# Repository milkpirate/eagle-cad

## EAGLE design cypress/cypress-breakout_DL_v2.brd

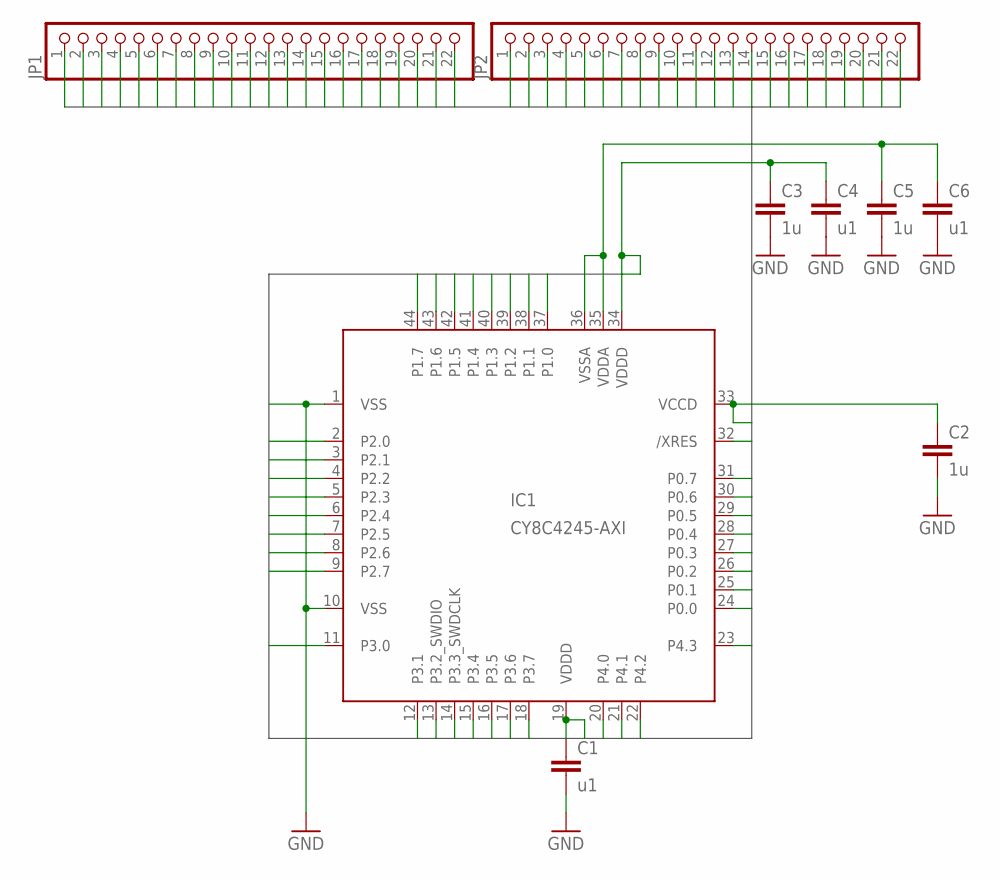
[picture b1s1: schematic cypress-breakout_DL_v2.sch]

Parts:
C1, C4, C6: u1; C0805K
C2, C3, C5: 1u; C0805K
IC1: CY8C4245-AXI; 44-TQFP-0.8
JP1, JP2: PINHD-1X22; 1X22

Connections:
#XRES: IC1.32 (/XRES), JP2.10
GND: C1.2, C2.2, C3.2, C4.2, C5.2, C6.2
P0.0: IC1.24 (P0.0), JP2.2
P0.1: IC1.25 (P0.1), JP2.3
P0.2: IC1.26 (P0.2), JP2.4
P0.3: IC1.27 (P0.3), JP2.5
P0.4: IC1.28 (P0.4), JP2.6
P0.5: IC1.29 (P0.5), JP2.7
P0.6: IC1.30 (P0.6), JP2.8
P0.7: IC1.31 (P0.7), JP2.9
P1.0: IC1.37 (P1.0), JP2.15
P1.1: IC1.38 (P1.1), JP2.16
P1.2: IC1.39 (P1.2), JP2.17
P1.3: IC1.40 (P1.3), JP2.18
P1.4: IC1.41 (P1.4), JP2.19
P1.5: IC1.42 (P1.5), JP2.20
P1.6: IC1.43 (P1.6), JP2.21
P1.7: IC1.44 (P1.7), JP2.22
P2.0: IC1.2 (P2.0), JP1.2
P2.1: IC1.3 (P2.1), JP1.3
P2.2: IC1.4 (P2.2), JP1.4
P2.3: IC1.5 (P2.3), JP1.5
P2.4: IC1.6 (P2.4), JP1.6
P2.5: IC1.7 (P2.5), JP1.7
P2.6: IC1.8 (P2.6), JP1.8
P2.7: IC1.9 (P2.7), JP1.9
P3.0: IC1.11 (P3.0), JP1.11
P3.1: IC1.12 (P3.1), JP1.12
P3.2: IC1.13 (P3.2_SWDIO), JP1.13
P3.3: IC1.14 (P3.3_SWDCLK), JP1.14
P3.4: IC1.15 (P3.4), JP1.15
P3.5: IC1.16 (P3.5), JP1.16
P3.6: IC1.17 (P3.6), JP1.17
P3.7: IC1.18 (P3.7), JP1.18
P4.0: IC1.20 (P4.0), JP1.20
P4.1: IC1.21 (P4.1), JP1.21
P4.2: IC1.22 (P4.2), JP1.22
P4.3: IC1.23 (P4.3), JP2.1
VCCD: C2.1, IC1.33 (VCCD), JP2.11
VDDA: C5.1, C6.1, IC1.35 (VDDA), JP2.13
VDDD: C1.1, C3.1, C4.1, IC1.19 (VDDD), IC1.34 (VDDD), JP1.19, JP2.12
VSS: IC1.1 (VSS), IC1.10 (VSS), JP1.1, JP1.10
VSSA: IC1.36 (VSSA), JP2.14

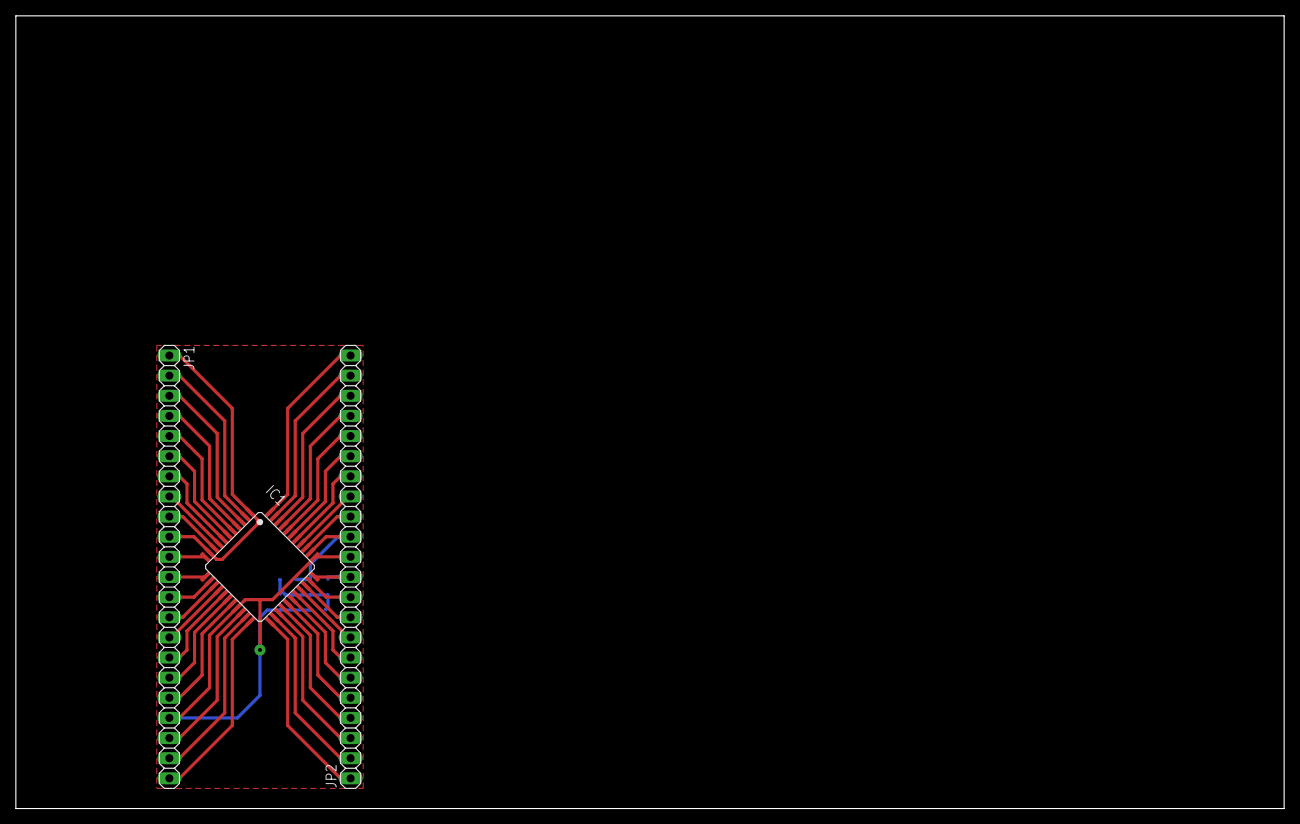
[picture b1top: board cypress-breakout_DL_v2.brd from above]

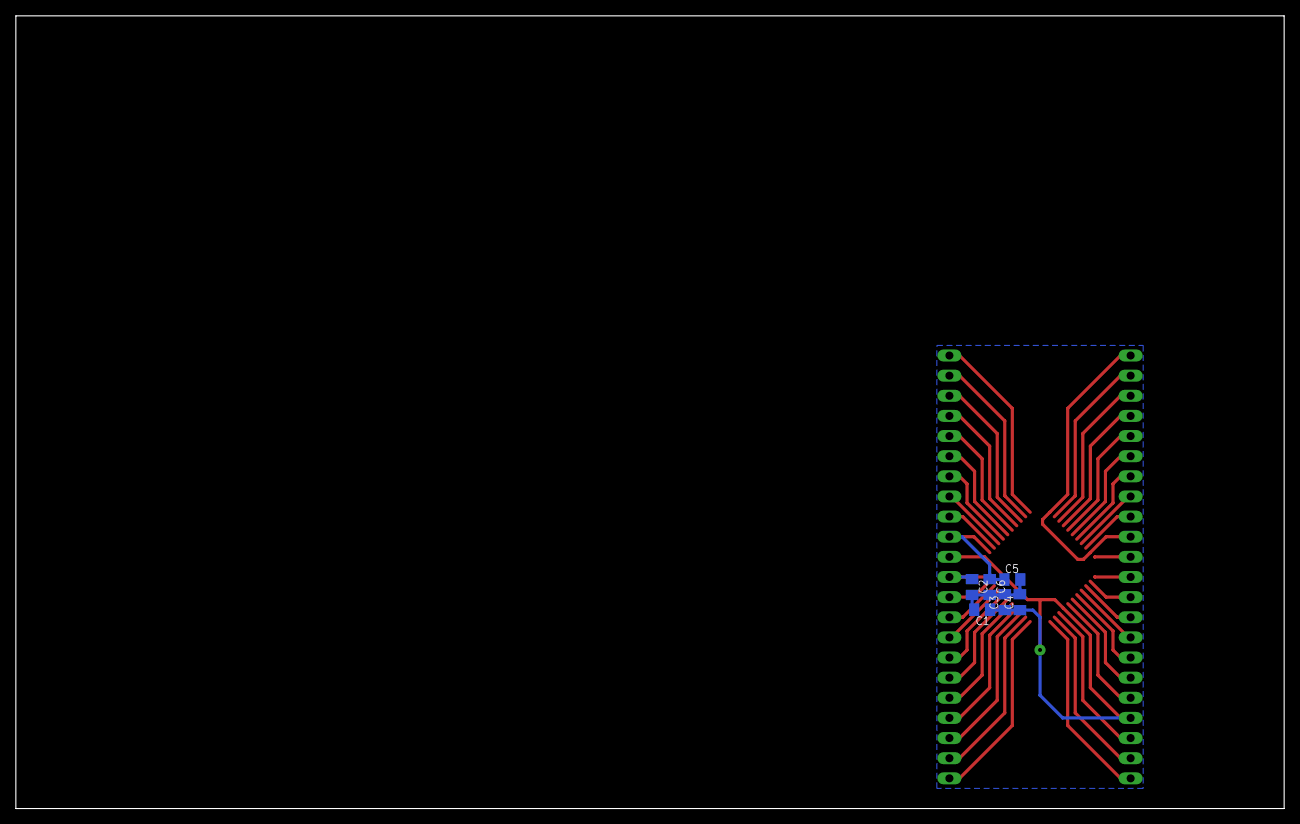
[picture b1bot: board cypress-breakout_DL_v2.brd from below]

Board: 2 copper layers, 160.0 x 100.0 mm, 9 parts (6 on the bottom side), 43 nets.

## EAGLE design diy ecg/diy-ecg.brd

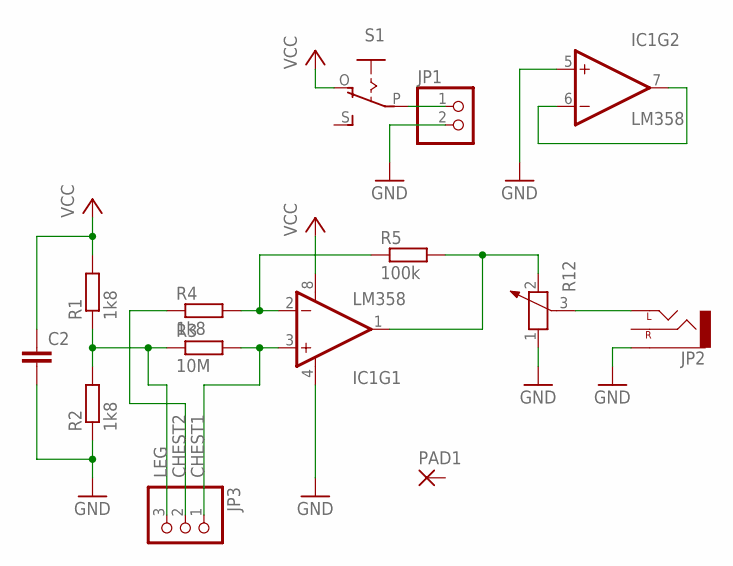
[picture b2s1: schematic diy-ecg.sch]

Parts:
C2: C-EU025-025X050; C025-025X050
IC1: LM358; DIP08
JP1: PINHD-1X2; 1X02
JP2: AUDIO-JACKPIN-HOLES; AUDIO-JACK-HOLES
JP3: PINHD-1X3; 1X03
PAD1: 3,81/1,4
R1, R2, R4: 1k8; 0204/7
R3: 10M; 0204/7
R5: 100k; 0204/7
R12: POTENTIOMETER_PT-10; PT-10
S1: EG1218S; EG1218

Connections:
CHEST1: IC1.3 (+IN), JP3.1, R3.2
CHEST2: JP3.2, R4.1
GND: C2.2, IC1.4 (V-), IC1.5 (+IN), JP1.2, JP2.GND (SLEEVE), R2.1, R12.1
LEG: JP3.3, R1.1, R2.2, R3.1
unnamed: JP1.1, S1.P
unnamed: IC1.1 (OUT), R5.2, R12.2
unnamed: IC1.2 (-IN), R4.2, R5.1
unnamed: IC1.6 (-IN), IC1.7 (OUT)
unnamed: JP2.L1- (LEFT), JP2.L2- (LEFT), R12.3
VCC: C2.1, IC1.8 (V+), R1.2, S1.O

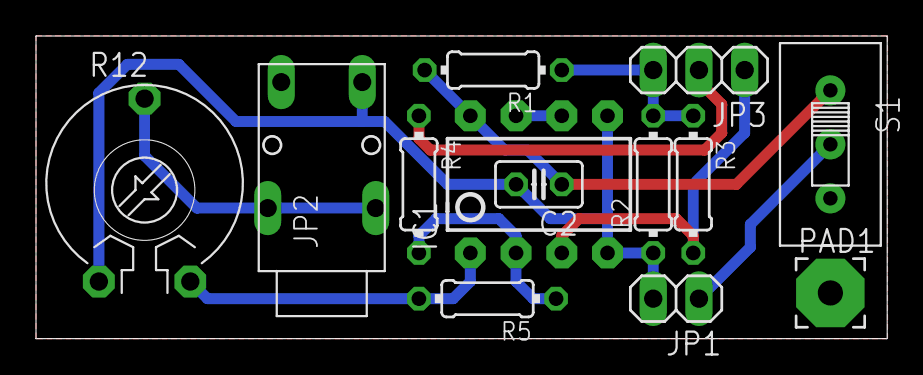
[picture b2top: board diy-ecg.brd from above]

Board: 2 copper layers, 47.3 x 16.8 mm, 13 parts (0 on the bottom side), 10 nets.

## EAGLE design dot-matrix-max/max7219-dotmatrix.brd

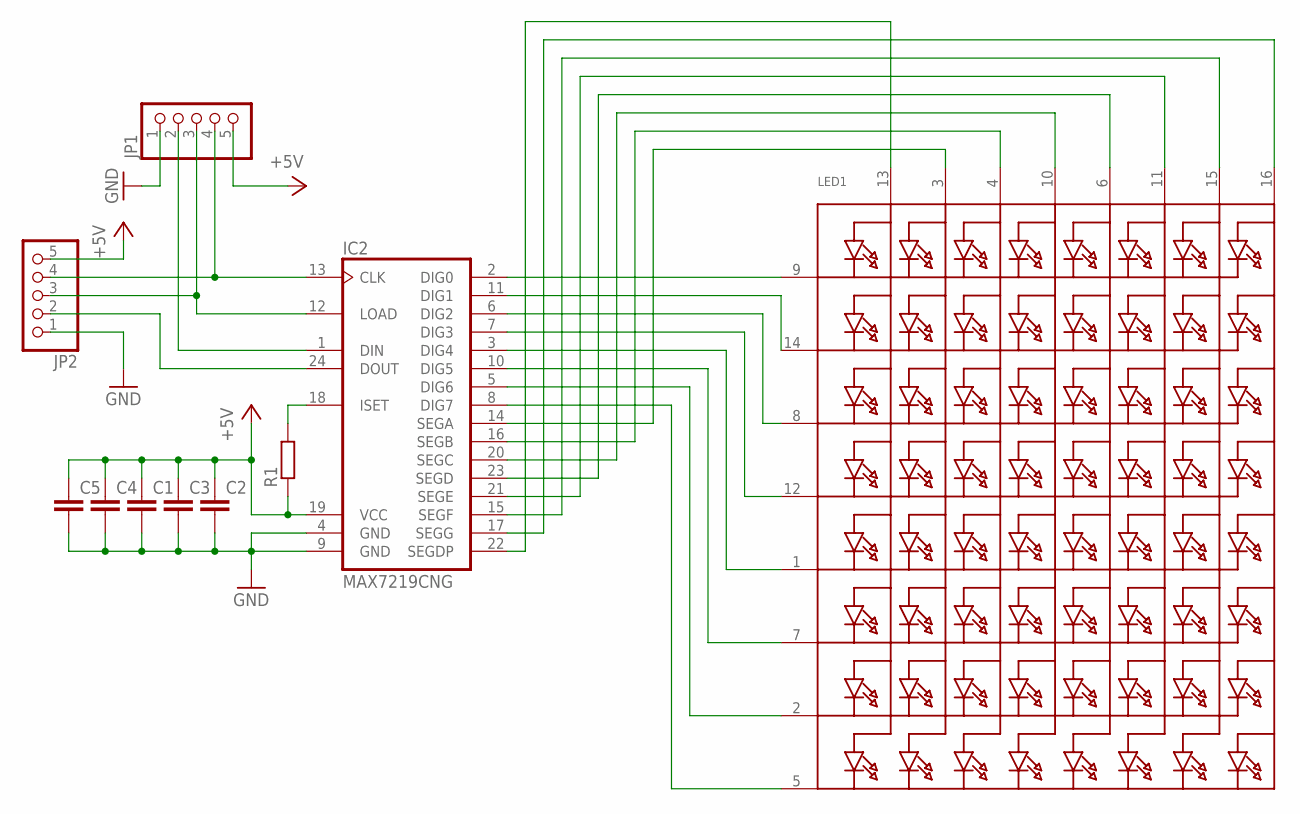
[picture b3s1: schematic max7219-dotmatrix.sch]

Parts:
C1, C2, C3, C4, C5: C-EUC0805K; C0805K
IC2: MAX7219CNG; DIL24-3
JP1, JP2: PINHD-1X5/90; 1X05/90
LED1: SEGMENT_8X8_ROWCATHODEM12A881UR; SEGMENT_BL-M12A881UR
R1: R-EU_M0805; M0805

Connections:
+5V: C1.1, C2.1, C3.1, C4.1, C5.1, IC2.19 (VCC), JP1.5, JP2.5, R1.1
GND: C1.2, C2.2, C3.2, C4.2, C5.2, IC2.4 (GND), IC2.9 (GND), JP1.1, JP2.1
unnamed: IC2.2 (DIG0), LED1.9 (K1)
unnamed: IC2.11 (DIG1), LED1.14 (K2)
unnamed: IC2.6 (DIG2), LED1.8 (K3)
unnamed: IC2.7 (DIG3), LED1.12 (K4)
unnamed: IC2.3 (DIG4), LED1.1 (K5)
unnamed: IC2.10 (DIG5), LED1.7 (K6)
unnamed: IC2.5 (DIG6), LED1.2 (K7)
unnamed: IC2.8 (DIG7), LED1.5 (K8)
unnamed: IC2.14 (SEGA), LED1.3 (A2)
unnamed: IC2.16 (SEGB), LED1.4 (A3)
unnamed: IC2.20 (SEGC), LED1.10 (A4)
unnamed: IC2.23 (SEGD), LED1.6 (A5)
unnamed: IC2.21 (SEGE), LED1.11 (A6)
unnamed: IC2.15 (SEGF), LED1.15 (A7)
unnamed: IC2.17 (SEGG), LED1.16 (A8)
unnamed: IC2.22 (SEGDP), LED1.13 (A1)
unnamed: IC2.24 (DOUT), JP2.2
unnamed: IC2.13 (CLK), JP1.4, JP2.4
unnamed: IC2.12 (LOAD), JP1.3, JP2.3
unnamed: IC2.18 (ISET), R1.2
unnamed: IC2.1 (DIN), JP1.2

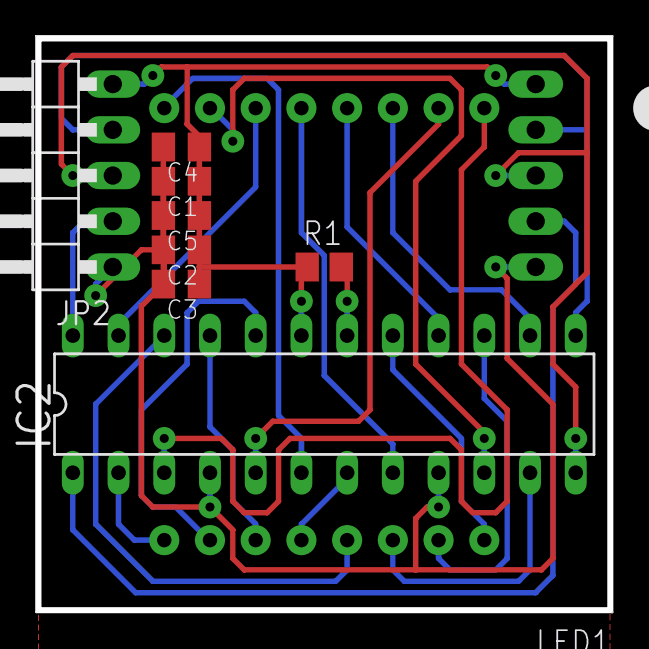
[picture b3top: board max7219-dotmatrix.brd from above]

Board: 2 copper layers, 31.7 x 31.7 mm, 10 parts (1 on the bottom side), 23 nets.

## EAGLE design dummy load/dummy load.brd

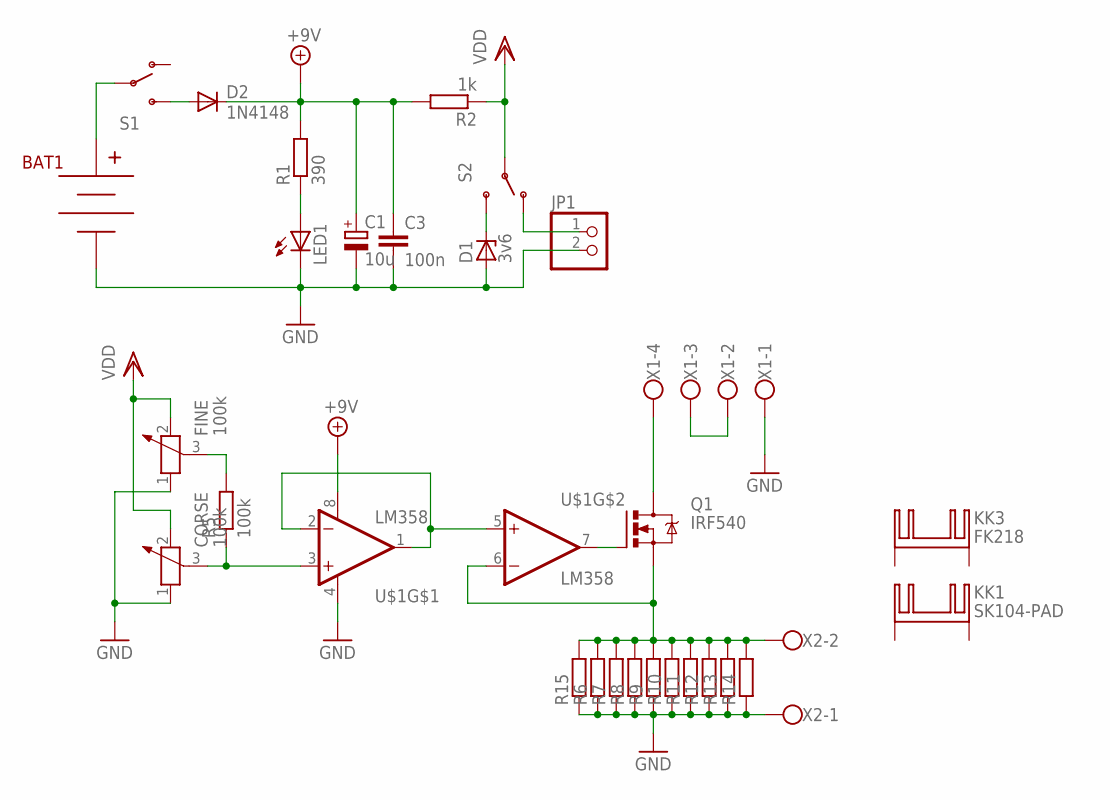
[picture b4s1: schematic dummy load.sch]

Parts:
BAT1: BC9VPC
C1: 10u; TT2D5L
C3: 100n; C025-025X050
CORSE: 100k; PT-10
D1: 3v6; ZDIO-5
D2: 1N4148; D-2.5
FINE: 100k; PT-10
JP1: PINHD-1X2; 1X02
KK1: SK104-PAD
KK3: FK218
LED1: LED5MM
Q1: IRF540; TO220BV
R1: 390; 0207/2V
R2: 1k; 0204/7
R5: 100k; 0204/7
R6, R7, R8, R9, R10, R11, R12, R13, R14, R15: R-EU_0207/7; 0207/7
S1, S2: SWITCH-SPSTPTH; SWITCH-SPDT
U$1: LM358; DIP08
X1: W237-4
X2: W237-102

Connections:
+9V: C1.+, C3.1, D2.C, R1.2, R2.2, U$1.8 (V+)
GND: BAT1.V-, C1.-, C3.2, CORSE.1, D1.A, FINE.1, JP1.2, LED1.K (C), R6.1, R7.1, R8.1, R9.1, R10.1, R11.1, R12.1, R13.1, R14.1, R15.1, U$1.4 (V-), X1.1, X2.1
unnamed: U$1.1 (OUT), U$1.2 (-IN), U$1.5 (+IN)
unnamed: CORSE.3, R5.1, U$1.3 (+IN)
unnamed: LED1.A, R1.1
unnamed: FINE.3, R5.2
unnamed: BAT1.V+, S1.2
unnamed: Q1.D, X1.4
unnamed: X1.2, X1.3
unnamed: D2.A, S1.3 (S)
unnamed: Q1.G, U$1.7 (OUT)
unnamed: D1.C, S2.3 (S)
unnamed: JP1.1, S2.1 (O)
unnamed: Q1.S, R6.2, R7.2, R8.2, R9.2, R10.2, R11.2, R12.2, R13.2, R14.2, R15.2, U$1.6 (-IN), X2.2
VDD: CORSE.2, FINE.2, R2.1, S2.2

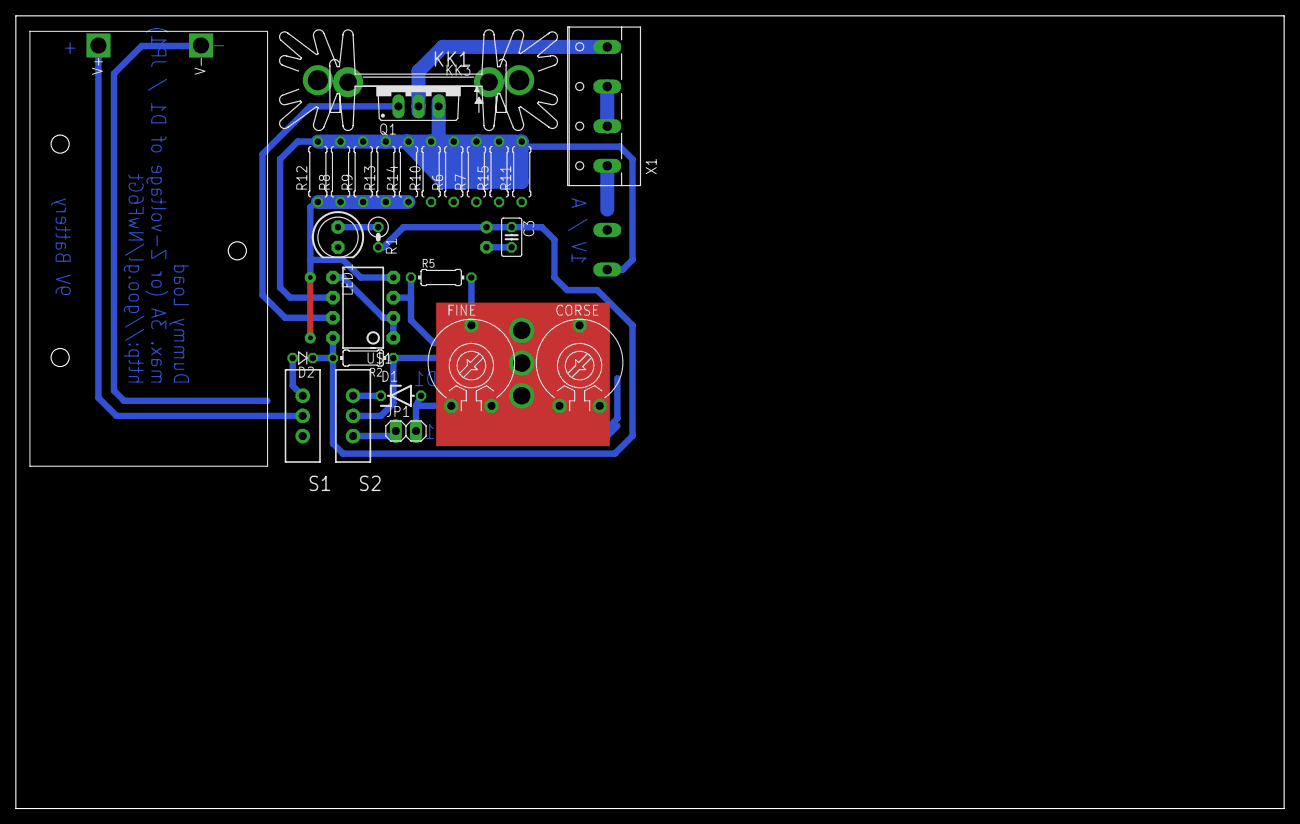
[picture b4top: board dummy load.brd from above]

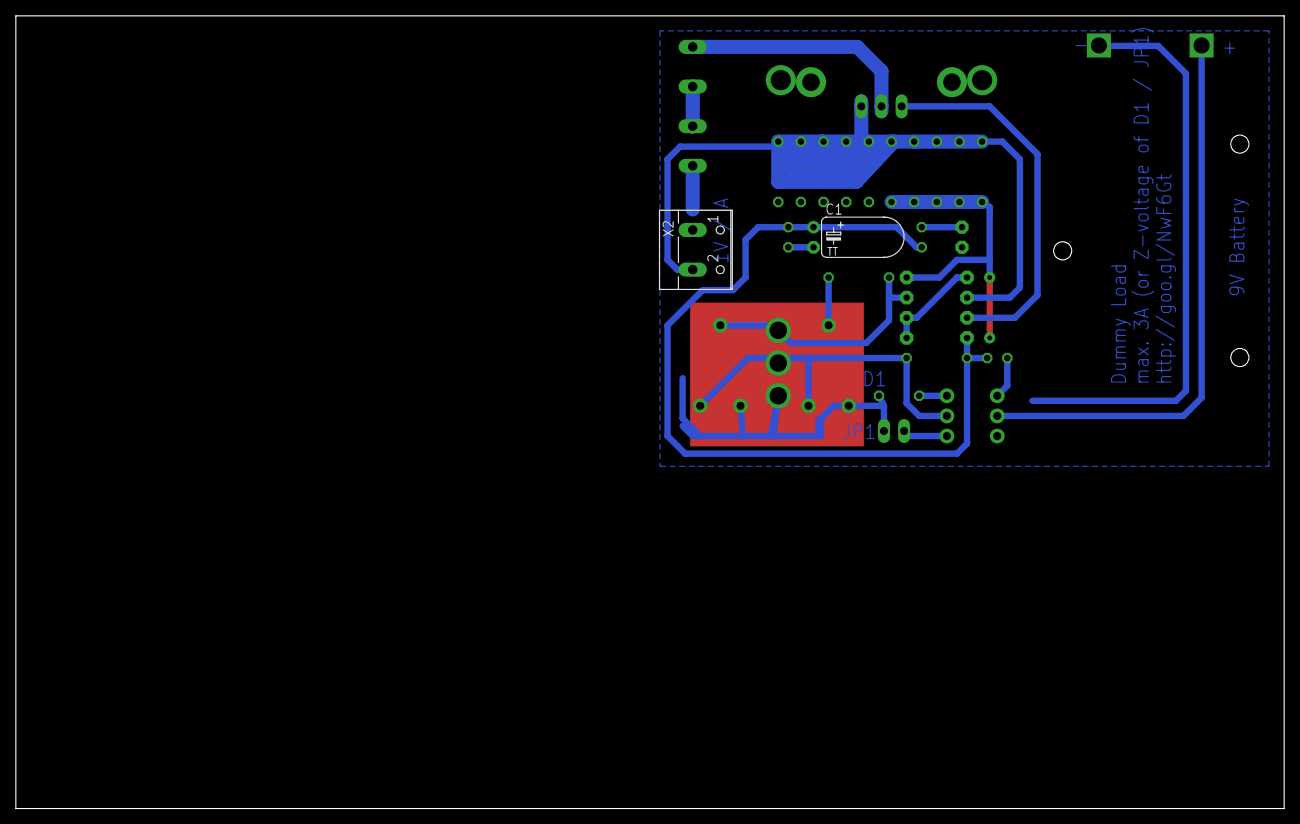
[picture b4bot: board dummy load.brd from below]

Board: 2 copper layers, 160.0 x 100.0 mm, 30 parts (2 on the bottom side), 15 nets.

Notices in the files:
parts and their libraries:
SparkFun-AnalogIC: Licensing:Creative Commons ShareAlike 4.0 International - https://creativecommons.org/licenses/by-sa/4.0
SparkFun: Licensing: CC v3.0 Share-Alike You are welcome to use this library for commercial purposes.
